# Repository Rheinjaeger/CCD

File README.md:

This is the repository for CCD Small Satellite Readout System Project.

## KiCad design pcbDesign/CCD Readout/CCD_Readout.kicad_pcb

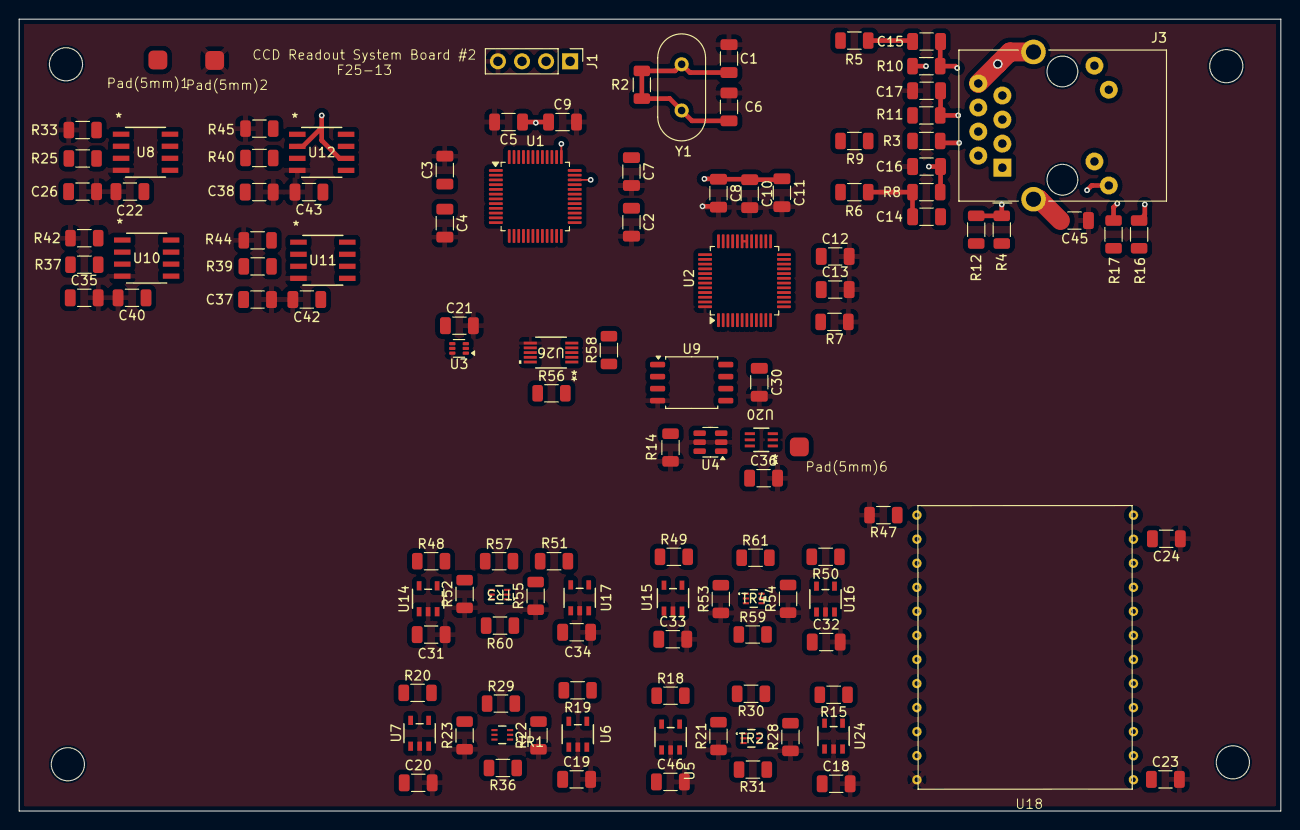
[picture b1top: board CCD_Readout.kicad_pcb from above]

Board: 6 copper layers, 133.2 x 83.6 mm, 118 parts (0 on the bottom side), 91 nets.

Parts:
C1, C6: 18pF; C_1206_3216Metric
C2: 1u; C_1206_3216Metric
C3, C8, C22, C35, C37, C38: 10u; C_1206_3216Metric
C4, C5, C7, C9, C10, C11, C18, C19, C20, C21, C23, C24, C26, C30, C31, C32, C33, C34, C36, C40, C42, C43, C46: 0.1u; C_1206_3216Metric
C12, C16: 10nF; C_1206_3216Metric
C13: 4.7nF; C_1206_3216Metric
C14, C15: 6.8nF; C_1206_3216Metric
C17: 22nF; C_1206_3216Metric
C45: 1nF; C_1206_3216Metric
J1: Conn_01x04_Pin; PinHeader_1x04_P2.54mm_Vertical
J3: RJ45_Amphenol_RJMG1BD3B8K1ANR
Pad(5mm)1, Pad(5mm)2, Pad(5mm)6: 2mm Pad
R2: 1M; R_1206_3216Metric
R3, R4, R5, R6: 33; R_1206_3216Metric
R7: 12.4k; R_1206_3216Metric
R8, R9, R10, R11, R12: 49R9; R_1206_3216Metric
R14, R15, R18, R19, R20, R48, R49, R50, R51, R56, R58: 10k; R_1206_3216Metric
R16, R17: 330R; R_1206_3216Metric
R21, R22, R23, R28, R29, R30, R31, R33, R36, R42, R44, R45, R52, R53, R54, R55, R57, R59, R60, R61: 100k; R_1206_3216Metric
R25: 68k; R_1206_3216Metric
R37: 180k; R_1206_3216Metric
R39: 470k; R_1206_3216Metric
R40: 750k; R_1206_3216Metric
R47: 5k; R_1206_3216Metric
TR1, TR2, TR3, TR4: EM6K7T2R; TRANS_EM6_ROM
U1: STM32L052C8Tx; LQFP-48_7x7mm_P0.5mm
U2: W5500; LQFP-48_7x7mm_P0.5mm
U3: TMP20AIDRL; SOT-563
U4: LT6200; TSOT-23-6
U5, U6, U7, U14, U15, U16, U17, U24: UCC27517ADBVR; DBV5_TEX
U8, U10, U11, U12: OPA2994IDR; SOIC8_3P98X5_TEX
U9: W25X20CLSN; SOP-8_5.28x5.23mm_P1.27mm
U18: CCD Sensor
U20: NC7SB3157P6X; SC-70_6L_ONS-M
U26: ISL22316WFU10Z; MSOP10_3X3_INR
Y1: Crystal; Crystal_HC49-U_Vertical

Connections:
+28V: C22.1, C23.1, C24.2, C26.1, C35.1, C37.1, C38.1, C40.1, C42.1, C43.1, Pad(5mm)1.1 (In/Out), R25.1, R37.1, R39.1, R40.1, U8.7 (VCC+), U18.1 (ABD), U18.11 (OD)
/+3.3V: C2.1, C3.1, C4.1, C5.1, C7.1, C8.1, C9.1, C10.1, C11.1, C21.1, C30.1, J1.3, J3.L1, J3.L4, R9.1, R11.1, R12.1, R56.1, R58.2, U1.1 (VDD), U1.9 (VDDA), U1.24 (VDD), U1.48 (VDD), U2.4 (AVDD), U2.8 (AVDD), U2.11 (AVDD), U2.15 (AVDD), U2.17 (AVDD), U2.21 (AVDD), U2.28 (VDD), U3.4 (V_{DD}), U9.7 (~HOLD), U9.8 (VCC), U12.2 (IN-), U12.6 (OUT), U18.5 (OG), U26.10 (VCC)
/+5V: C36.1, U4.6 (V+), U11.2 (IN-), U11.6 (OUT), U12.7 (VCC+), U20.5 (VCC)
/+10V: R29.1, R36.1, R61.1, U10.2 (IN-), U10.6 (OUT), U11.7 (VCC+), U18.7 (SS), U18.18 (SS)
/+12V: C18.1, C19.1, C20.1, C31.1, C32.1, C33.1, C34.1, C46.1, R30.2, R31.1, U5.1 (VDD), U5.3 (IN+), U6.1 (VDD), U6.3 (IN+), U7.1 (VDD), U7.3 (IN+), U14.1 (VDD), U14.3 (IN+), U15.1 (VDD), U15.3 (IN+), U16.1 (VDD), U16.3 (IN+), U17.1 (VDD), U17.3 (IN+), U24.1 (VDD), U24.3 (IN+)
/+15V: R57.1, R59.1, R60.1
/+17V: U8.2 (IN-), U8.6 (OUT), U10.7 (VCC+), U18.14 (RD)
/ACTLED: R16.2, U2.27 (ACTLED)
/ADC_Select: U1.11 (PA1), U20.6 (S)
/Amp_Sig_1: R14.1, U4.4 (-), U26.9 (RH)
/Amp_Sig_2: U1.10 (PA0), U4.1, U26.8 (RW)
/CCD_OUT: R47.1, U18.13 (OSR), U20.3 (B0)
/CD_Gate: U1.33 (PA12), U24.4 (IN-)
/Charge_Dump: R30.1, TR2.6 (Drain), U18.20 (DG)
/Digipot_SHDN#: U1.32 (PA11), U26.5 (*SHDN)
/E_PM0: U1.46 (PB9), U2.45 (PMODE0)
/E_PM1: U1.45 (PB8), U2.44 (PMODE1)
/E_PM2: U1.43 (PB7), U2.43 (PMODE2)
/Ethernet_CE: U1.14 (PA4), U2.32 (~SCS)
/Ethernet_INTn: U1.29 (PA8), U2.36 (~INT)
/Ethernet_MISO: U1.16 (PA6), U2.34 (MISO)
/Ethernet_MOSI: U1.17 (PA7), U2.35 (MOSI)
/Ethernet_RSTn: U1.21 (PB10), U2.37 (~RST)
/Ethernet_SCLK: U1.15 (PA5), U2.33 (SCLK)
/Flash_CS: U1.25 (PB12), U9.1 (~CS)
/Flash_MISO: U1.27 (PB14), U9.2 (DO(IO1))
/Flash_MOSI: U1.28 (PB15), U9.5 (DI(IO0))
/Flash_SCK: U1.26 (PB13), U9.6 (SCK)
/I1: U1.18 (PB0), U5.4 (IN-)
/I1_to_CCD: R57.2, TR3.3 (Drain), U18.4 (I1), U18.21 (I1)
/I2: U1.19 (PB1), U7.4 (IN-)
/I2C1_SCL: R56.2, U1.30 (PA9), U26.1 (SCL)
/I2C1_SDA: R58.1, U1.31 (PA10), U26.2 (SDA)
/I2_to_CCD: R60.2, TR3.6 (Drain), U18.3 (I2), U18.22 (I2)
/I3: U1.20 (PB2), U6.4 (IN-)
/I3_to_CCD: R59.2, TR4.3 (Drain), U18.2 (I3), U18.23 (I3)
/LINKLED: R17.2, U2.25 (LINKLED)
/R: U1.42 (PB6), U17.4 (IN-)
/R1: U1.39 (PB3), U16.4 (IN-)
/R1_to_CCD: R61.2, TR4.6 (Drain), U18.15 (R1R)
/R2: U1.40 (PB4), U15.4 (IN-)
/R2_to_CCD: R29.2, TR1.3 (Drain), U18.16 (R2R)
/R3: U1.41 (PB5), U14.4 (IN-)
/R3_to_CCD: R36.2, TR1.6 (Drain), U18.17 (R3)
/R_to_CCD: R31.2, TR2.3 (Drain), U18.8 (R)
/SWCLK: J1.2, U1.37 (PA14)
/SWDIO: J1.1, U1.34 (PA13)
/Temp_2: U1.13 (PA3), U3.3 (V_{OUT})
//WP: U1.22 (PB11), U9.3 (~WP)
GND: C1.2, C2.2, C3.2, C4.2, C5.2, C6.2, C7.2, C8.2, C9.2, C10.2, C11.2, C12.2, C13.2, C16.2, C17.2, C18.2, C19.2, C20.2, C21.2, C22.2, C23.2, C24.1, C26.2, C30.2, C31.2, C32.2, C33.2, C34.2, C35.2, C36.2, C37.2, C38.2, C40.2, C42.2, C43.2, C45.1, C46.2, J1.4, Pad(5mm)2.1 (In/Out), R7.1, R14.2, R21.1, R22.1, R23.1, R28.1, R33.1, R42.1, R44.1, R45.1, R47.2, R52.1, R53.1, R54.1, R55.1, TR1.1 (Source), TR1.4 (Source), TR2.1 (Source), TR2.4 (Source), TR3.1 (Source), TR3.4 (Source), TR4.1 (Source), TR4.4 (Source), U1.8 (VSSA), U1.23 (VSS), U1.35 (VSS), U1.44 (BOOT0), U1.47 (VSS), U2.3 (AGND), U2.9 (AGND), U2.14 (AGND), U2.16 (AGND), U2.19 (AGND), U2.29 (GND), U2.48 (AGND), U3.2 (GND), U3.6 (GND), U4.2 (V-), U4.5 (~ENABLE), U5.2 (GND), U6.2 (GND), U7.2 (GND), U8.4 (VCC-), U9.4 (GND), U10.4 (VCC-), U11.4 (VCC-), U12.4 (VCC-), U14.2 (GND), U15.2 (GND), U16.2 (GND), U17.2 (GND), U18.24 (ABG), U20.2 (GND), U24.2 (GND), U26.3 (A1), U26.4 (A0), U26.6 (GND), U26.7 (RL)
GNDPWR: C45.2, J3.R8, J3.SH
unnamed: C14.1, R6.2, R8.1
unnamed: C15.1, R5.2
unnamed: J3.L2, R16.1
unnamed: J3.L3, R17.1
unnamed: C16.1, J3.R5 (RCT), R8.2, R10.2
unnamed: C14.2, J3.R3 (RD+)
unnamed: C15.2, J3.R6 (RD-), R10.1
unnamed: C17.1, J3.R4 (TCT), R11.2
unnamed: J3.R1 (TD+), R4.2, R12.2
unnamed: J3.R2 (TD-), R3.2, R9.2
unnamed: Pad(5mm)6.1 (In/Out), U20.1 (B1)
unnamed: R15.2, R28.2, TR2.5 (Gate)
unnamed: R18.2, R21.2, TR2.2 (Gate)
unnamed: R19.2, R22.2, TR1.2 (Gate)
unnamed: R20.2, R23.2, TR1.5 (Gate)
unnamed: R48.2, R52.2, TR3.5 (Gate)
unnamed: R49.2, R53.2, TR4.2 (Gate)
unnamed: R50.2, R54.2, TR4.5 (Gate)
unnamed: R51.2, R55.2, TR3.2 (Gate)
unnamed: C12.1, U2.22 (1V2O)
unnamed: R7.2, U2.10 (EXRES1)
unnamed: R5.1, U2.5 (RXN)
unnamed: R6.1, U2.6 (RXP)
unnamed: C13.1, U2.20 (TOCAP)
unnamed: R3.1, U2.1 (TXN)
unnamed: R4.1, U2.2 (TXP)
unnamed: C1.1, C6.1, R2.1, R2.2, U2.30 (XI/CLKIN), U2.31 (XO), Y1.1, Y1.2
unnamed: R18.1, U5.5 (OUT)
unnamed: R19.1, U6.5 (OUT)
unnamed: R20.1, U7.5 (OUT)
unnamed: R25.2, R33.2, U8.3 (IN+)
unnamed: R37.2, R42.2, U10.3 (IN+)
unnamed: R39.2, R44.2, U11.3 (IN+)
unnamed: R40.2, R45.2, U12.3 (IN+)
unnamed: R48.1, U14.5 (OUT)
unnamed: R49.1, U15.5 (OUT)
unnamed: R50.1, U16.5 (OUT)
unnamed: R51.1, U17.5 (OUT)
unnamed: U4.3 (+), U20.4 (A)
unnamed: R15.1, U24.5 (OUT)

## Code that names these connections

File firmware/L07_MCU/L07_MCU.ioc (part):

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Mcu.Name=STM32L073R(B-Z)Tx
Mcu.Package=LQFP64
Mcu.UserName=STM32L073RZTx
PA0.GPIOParameters=GPIO_Label
PA0.GPIO_Label=PreAmp_Out
PA0.Signal=GPIO_Output
PA1.GPIOParameters=GPIO_Label
PA1.GPIO_Label=ADC_Select
PA1.Signal=GPIO_Output
PA10.Signal=I2C1_SDA
PA11.GPIOParameters=GPIO_Label
PA11.GPIO_Label=Digipot_SHDN\#
PA11.Signal=GPIO_Output
PA12.GPIOParameters=GPIO_Label
PA12.GPIO_Label=CD_Gate
PA12.Signal=GPIO_Output
PA13.Mode=Serial_Wire
PA13.Signal=SYS_SWDIO
PA14.Mode=Serial_Wire
PA14.Signal=SYS_SWCLK
PA3.GPIOParameters=GPIO_Label
PA3.GPIO_Label=Temp_2
PA3.Mode=IN3
PA3.Signal=ADC_IN3
PA4.GPIOParameters=GPIO_Label
PA4.GPIO_Label=Ethernet_CE
PA4.Signal=GPIO_Output
PA5.GPIOParameters=GPIO_Label
PA5.GPIO_Label=Ethernet_SCLK
PA5.Signal=SPI1_SCK
PA6.GPIOParameters=GPIO_Label
PA6.GPIO_Label=Ethernet_MISO
PA6.Signal=SPI1_MISO
PA7.GPIOParameters=GPIO_Label
PA7.GPIO_Label=Ethernet_MOSI
PA7.Signal=SPI1_MOSI
PA8.GPIOParameters=GPIO_Label
PA8.GPIO_Label=Ethernet_INTn
PA8.Signal=GPXTI8
PA9.Signal=I2C1_SCL
PB0.GPIOParameters=GPIO_Label
PB0.GPIO_Label=I1
PB0.Signal=GPIO_Output
PB1.GPIOParameters=GPIO_Label
PB1.GPIO_Label=I2
PB1.Signal=GPIO_Output
PB10.GPIOParameters=GPIO_Label
PB10.GPIO_Label=Ethernet_RSTn
PB10.Signal=GPIO_Output
PB11.GPIOParameters=GPIO_Label
PB11.GPIO_Label=_/WP
PB11.Signal=GPIO_Output
PB12.GPIOParameters=GPIO_Label
PB12.GPIO_Label=Flash_CS
PB12.Signal=GPIO_Output
PB13.GPIOParameters=GPIO_Label
PB13.GPIO_Label=Flash_SCK
PB13.Signal=SPI2_SCK
PB14.GPIOParameters=GPIO_Label
PB14.GPIO_Label=Flash_MISO
PB14.Signal=SPI2_MISO
PB15.GPIOParameters=GPIO_Label
PB15.GPIO_Label=Flash_MOSI
PB15.Signal=SPI2_MOSI
PB2.GPIOParameters=GPIO_Label
PB2.GPIO_Label=I3
PB2.Signal=GPIO_Output
PB3.GPIOParameters=GPIO_Label
PB3.GPIO_Label=R1
PB3.Signal=GPIO_Output
PB4.GPIOParameters=GPIO_Label
PB4.GPIO_Label=R2
PB4.Signal=GPIO_Output
PB5.GPIOParameters=GPIO_Label
PB5.GPIO_Label=R3
PB5.Signal=GPIO_Output
PB6.GPIOParameters=GPIO_Label
PB6.GPIO_Label=R
PB6.Signal=GPIO_Output
PB7.GPIOParameters=GPIO_Label
PB7.GPIO_Label=E_PM2
PB7.Signal=GPIO_Output
PB8.GPIOParameters=GPIO_Label
PB8.GPIO_Label=E_PM1
PB8.Signal=GPIO_Output
PB9.GPIOParameters=GPIO_Label
PB9.GPIO_Label=E_PM0
PB9.Signal=GPIO_Output
RCC.HSE_VALUE=8000000
RCC.SYSCLKFreq_VALUE=2097000
board=custom

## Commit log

2025-02-22 initial structure establishment
2025-02-24 Fake Image Generation Ver.0
2025-02-26 reciever.py for image networking completed
2025-03-03 Rename receiver.py to Receiver.py
2025-03-20 Updated Image Size
2025-04-07 Emulator working
2025-04-07 GUI Push 0
2025-04-08 Updated Python Version to 3.13
2025-06-10 Updated GUI
2025-09-11 Added file structure for firmware
2025-09-16 Updated firmware with proper MCU code
2025-09-25 Added CCD_Module, Temperature, Data_Integrity, Command_Handler, and W5500 module
2025-10-05 Added System controller header and source files and connected them to main loop
2025-10-07 Create CCD Readout
2025-10-07 Create placeholder
2025-10-07 Finished fixing errors with System controller, command handler and main
2025-10-07 Added python test and ethernet ping pong
2025-10-08 Added the network corrections
2025-10-08 Added wiznet library
2025-10-09 Added io library and integrated into main for UDP server
2025-10-29 Changed 12C
2025-11-04 Added W5500 Drivers, Stable GPIO 1.0 test build with SPI memory modules
2025-11-17 Added ethernet files and I2C setup
